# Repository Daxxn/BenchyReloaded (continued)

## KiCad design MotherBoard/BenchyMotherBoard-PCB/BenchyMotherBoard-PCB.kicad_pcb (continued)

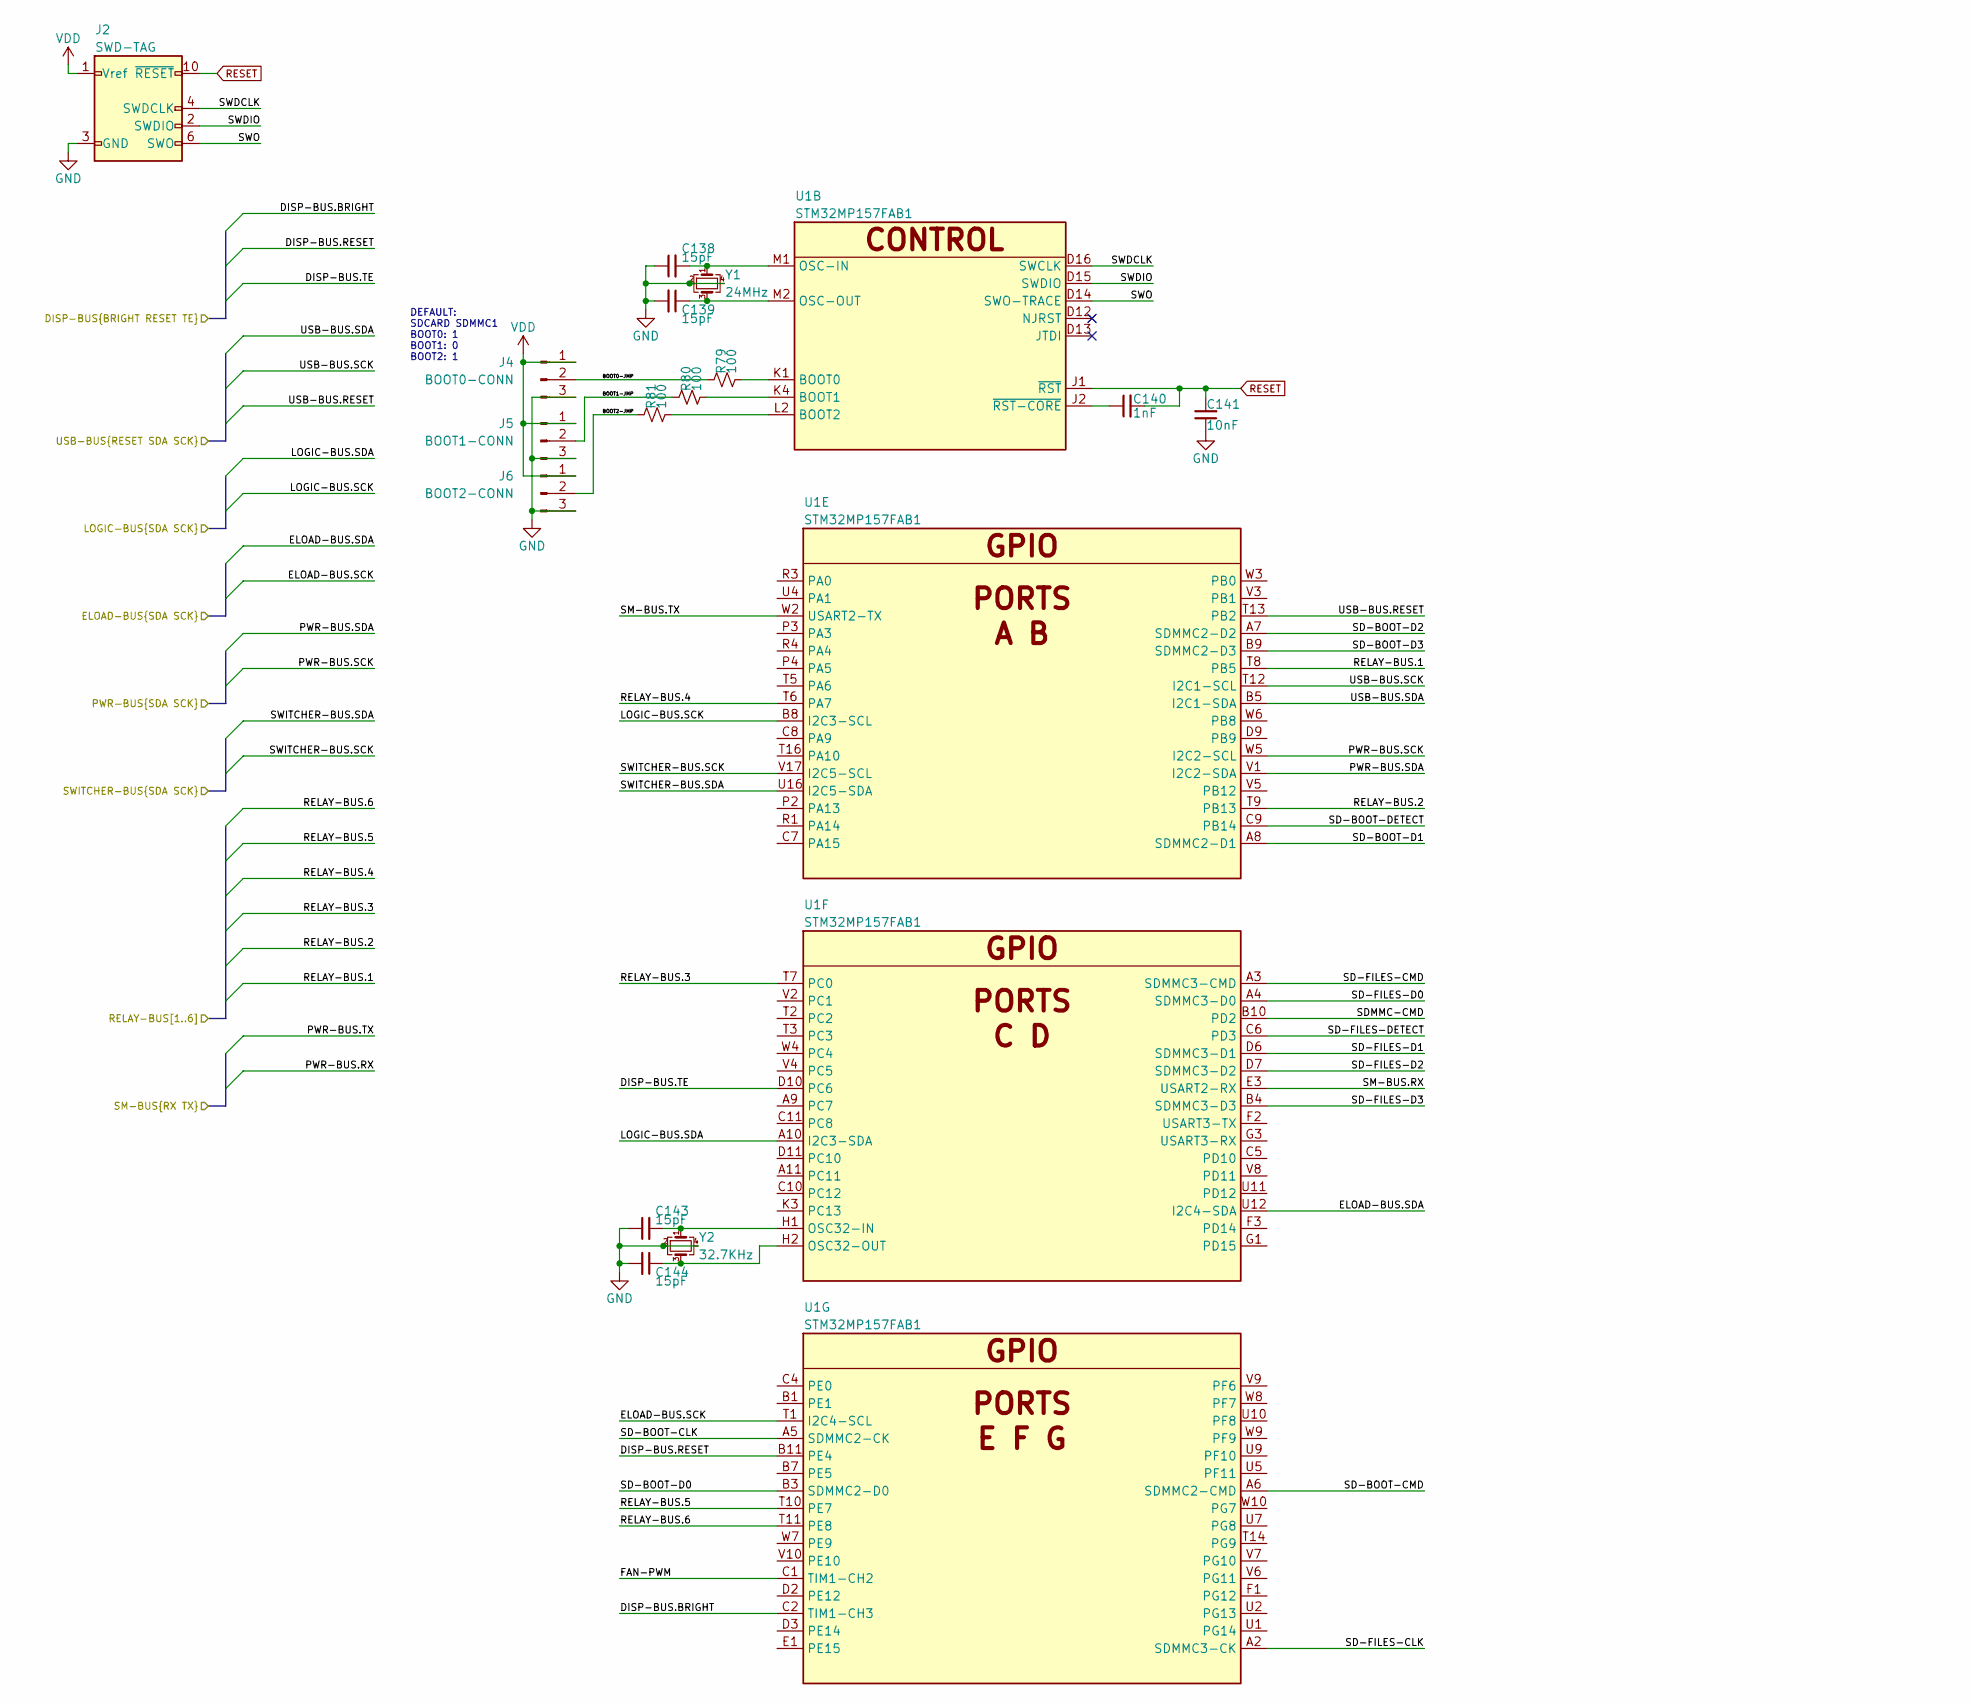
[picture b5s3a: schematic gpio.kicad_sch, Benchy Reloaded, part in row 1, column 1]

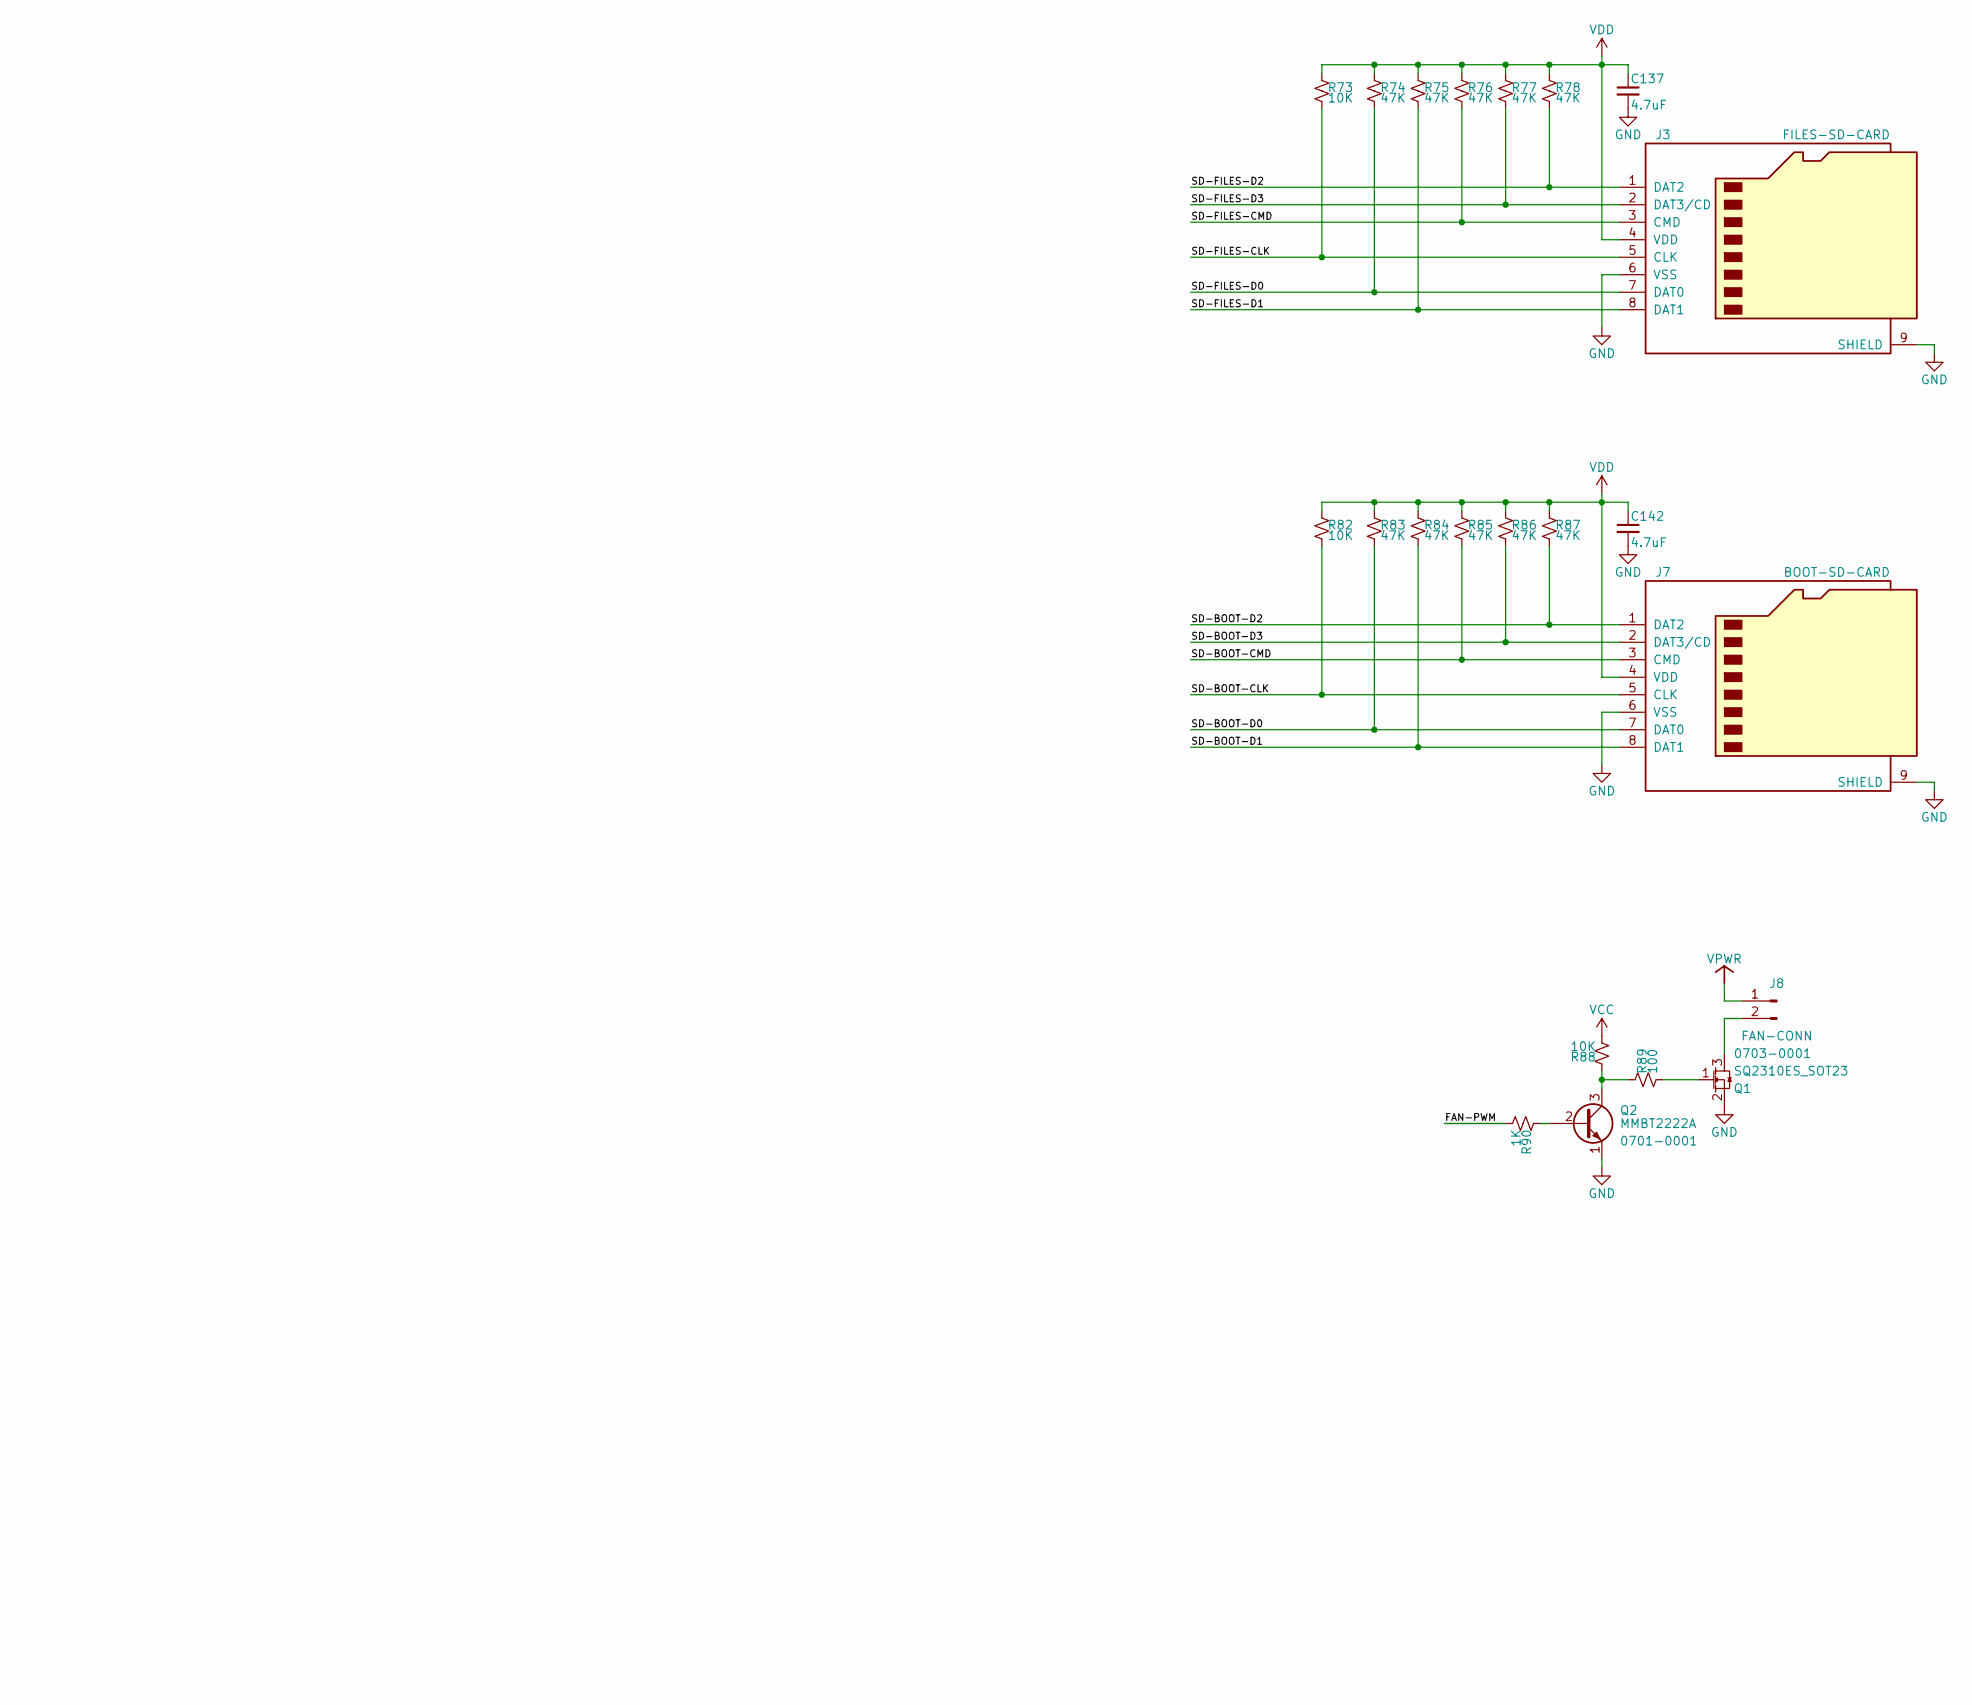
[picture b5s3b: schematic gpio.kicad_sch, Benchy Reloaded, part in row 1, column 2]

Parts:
C137, C142: 4.7uF; C_0805_2012Metric
C138, C139, C143, C144: 15pF; C_0402_1005Metric
C140: 1nF; C_0402_1005Metric
C141: 10nF; C_0402_1005Metric
J2: SWD-TAG; Tag-Connect_TC2050-IDC-FP_2x05_P1.27mm_Vertical
J3: FILES-SD-CARD; microSD_HC_Molex_47219-2001
J4: BOOT0-CONN; PinHeader_1x03_P2.54mm_Vertical
J5: BOOT1-CONN; PinHeader_1x03_P2.54mm_Vertical
J6: BOOT2-CONN; PinHeader_1x03_P2.54mm_Vertical
J7: BOOT-SD-CARD; microSD_HC_Molex_47219-2001
J8: FAN-CONN; PinHeader_1x02_P2.54mm_Vertical
Q1: SQ2310ES_SOT23; SOT-23; PartNumber 0703-0001
Q2: MMBT2222A; SOT-23; PartNumber 0701-0001
R73, R82, R88: 10K; R_0402_1005Metric
R74, R75, R76, R77, R78, R83, R84, R85, R86, R87: 47K; R_0402_1005Metric
R79, R80, R81, R89: 100; R_0402_1005Metric
R90: 1K; R_0402_1005Metric
U1: STM32MP157FAB1; LFBGA354-P0.8mm
Y1: 24MHz; Crystal_SMD_4Pin_3.2x2.5mm
Y2: 32.7KHz; Crystal_SMD_4Pin_3.2x2.5mm

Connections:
/COMMUNICATIONS/ELOAD-BUS.SCK: U1.T1 (I2C4-SCL); also elsewhere on the board
/COMMUNICATIONS/ELOAD-BUS.SDA: U1.U12 (I2C4-SDA); also elsewhere on the board
/COMMUNICATIONS/LOGIC-BUS.SCK: U1.B8 (I2C3-SCL); also elsewhere on the board
/COMMUNICATIONS/LOGIC-BUS.SDA: U1.A10 (I2C3-SDA); also elsewhere on the board
/COMMUNICATIONS/PWR-BUS.SCK: U1.W5 (I2C2-SCL); also elsewhere on the board
/COMMUNICATIONS/PWR-BUS.SDA: U1.V1 (I2C2-SDA); also elsewhere on the board
/COMMUNICATIONS/SWITCHER-BUS.SCK: U1.V17 (I2C5-SCL); also elsewhere on the board
/COMMUNICATIONS/SWITCHER-BUS.SDA: U1.U16 (I2C5-SDA); also elsewhere on the board
/INPUT | OUTPUT/BOOT0-JMP: J4.2, R79.1
/INPUT | OUTPUT/BOOT1-JMP: J5.2, R80.1
/INPUT | OUTPUT/BOOT2-JMP: J6.2, R81.1
/INPUT | OUTPUT/DISP-BUS.BRIGHT: U1.C2 (TIM1-CH3)
/INPUT | OUTPUT/DISP-BUS.RESET: U1.B11 (PE4); also elsewhere on the board
/INPUT | OUTPUT/DISP-BUS.TE: U1.D10 (PC6); also elsewhere on the board
/INPUT | OUTPUT/FAN-PWM: R90.2, U1.C1 (TIM1-CH2)
/INPUT | OUTPUT/RELAY-BUS.1: U1.T8 (PB5)
/INPUT | OUTPUT/RELAY-BUS.2: U1.T9 (PB13)
/INPUT | OUTPUT/RELAY-BUS.3: U1.T7 (PC0)
/INPUT | OUTPUT/RELAY-BUS.4: U1.T6 (PA7)
/INPUT | OUTPUT/RELAY-BUS.5: U1.T10 (PE7)
/INPUT | OUTPUT/RELAY-BUS.6: U1.T11 (PE8)
/INPUT | OUTPUT/SD-BOOT-CLK: J7.5 (CLK), R82.2, U1.A5 (SDMMC2-CK)
/INPUT | OUTPUT/SD-BOOT-CMD: J7.3 (CMD), R85.2, U1.A6 (SDMMC2-CMD)
/INPUT | OUTPUT/SD-BOOT-D0: J7.7 (DAT0), R83.2, U1.B3 (SDMMC2-D0)
/INPUT | OUTPUT/SD-BOOT-D1: J7.8 (DAT1), R84.2, U1.A8 (SDMMC2-D1)
/INPUT | OUTPUT/SD-BOOT-D2: J7.1 (DAT2), R87.2, U1.A7 (SDMMC2-D2)
/INPUT | OUTPUT/SD-BOOT-D3: J7.2 (DAT3/CD), R86.2, U1.B9 (SDMMC2-D3)
/INPUT | OUTPUT/SD-BOOT-DETECT: U1.C9 (PB14)
/INPUT | OUTPUT/SD-FILES-CLK: J3.5 (CLK), R73.2, U1.A2 (SDMMC3-CK)
/INPUT | OUTPUT/SD-FILES-CMD: J3.3 (CMD), R76.2, U1.A3 (SDMMC3-CMD)
/INPUT | OUTPUT/SD-FILES-D0: J3.7 (DAT0), R74.2, U1.A4 (SDMMC3-D0)
/INPUT | OUTPUT/SD-FILES-D1: J3.8 (DAT1), R75.2, U1.D6 (SDMMC3-D1)
/INPUT | OUTPUT/SD-FILES-D2: J3.1 (DAT2), R78.2, U1.D7 (SDMMC3-D2)
/INPUT | OUTPUT/SD-FILES-D3: J3.2 (DAT3/CD), R77.2, U1.B4 (SDMMC3-D3)
/INPUT | OUTPUT/SD-FILES-DETECT: U1.C6 (PD3)
/INPUT | OUTPUT/SDMMC-CMD: U1.B10 (PD2)
/INPUT | OUTPUT/SM-BUS.RX: U1.E3 (USART2-RX); also elsewhere on the board
/INPUT | OUTPUT/SM-BUS.TX: U1.W2 (USART2-TX); also elsewhere on the board
/INPUT | OUTPUT/SWDCLK: J2.4 (SWDCLK), U1.D16 (SWCLK)
/INPUT | OUTPUT/SWDIO: J2.2 (SWDIO), U1.D15 (SWDIO)
/INPUT | OUTPUT/SWO: J2.6 (SWO), U1.D14 (SWO-TRACE)
/INPUT | OUTPUT/USB-BUS.RESET: U1.T13 (PB2); also elsewhere on the board
/INPUT | OUTPUT/USB-BUS.SCK: U1.T12 (I2C1-SCL); also elsewhere on the board
/INPUT | OUTPUT/USB-BUS.SDA: U1.B5 (I2C1-SDA); also elsewhere on the board
GND: C137.2, C138.1, C139.2, C141.1, C142.2, C143.1, C144.2, J2.3 (GND), J2.5 (GND), J2.9 (GNDDetect), J3.6 (VSS), J3.9 (SHIELD), J4.3, J5.3, J6.3, J7.6 (VSS), J7.9 (SHIELD), Q1.2 (S), Q2.1 (E), Y1.2, Y1.4, Y2.2, Y2.4; also elsewhere on the board
unnamed: C138.2, U1.M1 (OSC-IN), Y1.1
unnamed: C139.1, U1.M2 (OSC-OUT), Y1.3
unnamed: C140.1, U1.J2 (~RST-CORE)
unnamed: C143.2, U1.H1 (OSC32-IN), Y2.1
unnamed: C144.1, U1.H2 (OSC32-OUT), Y2.3
unnamed: J8.2, Q1.3 (D)
unnamed: Q1.1 (G), R89.2
unnamed: Q2.2 (B), R90.1
unnamed: Q2.3 (C), R88.1, R89.1
unnamed: R79.2, U1.K1 (BOOT0)
unnamed: R80.2, U1.K4 (BOOT1)
unnamed: R81.2, U1.L2 (BOOT2)
RESET: C140.2, C141.2, J2.10 (~RESET), U1.J1 (~RST); also elsewhere on the board
VCC: R88.2; also elsewhere on the board
VDD: C137.1, C142.1, J2.1 (Vref), J3.4 (VDD), J4.1, J5.1, J6.1, J7.4 (VDD), R73.1, R74.1, R75.1, R76.1, R77.1, R78.1, R82.1, R83.1, R84.1, R85.1, R86.1, R87.1; also elsewhere on the board
VPWR: J8.1; also elsewhere on the board

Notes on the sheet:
DEFAULT: SDCARD SDMMC1 BOOT0: 1 BOOT1: 0 BOOT2: 1

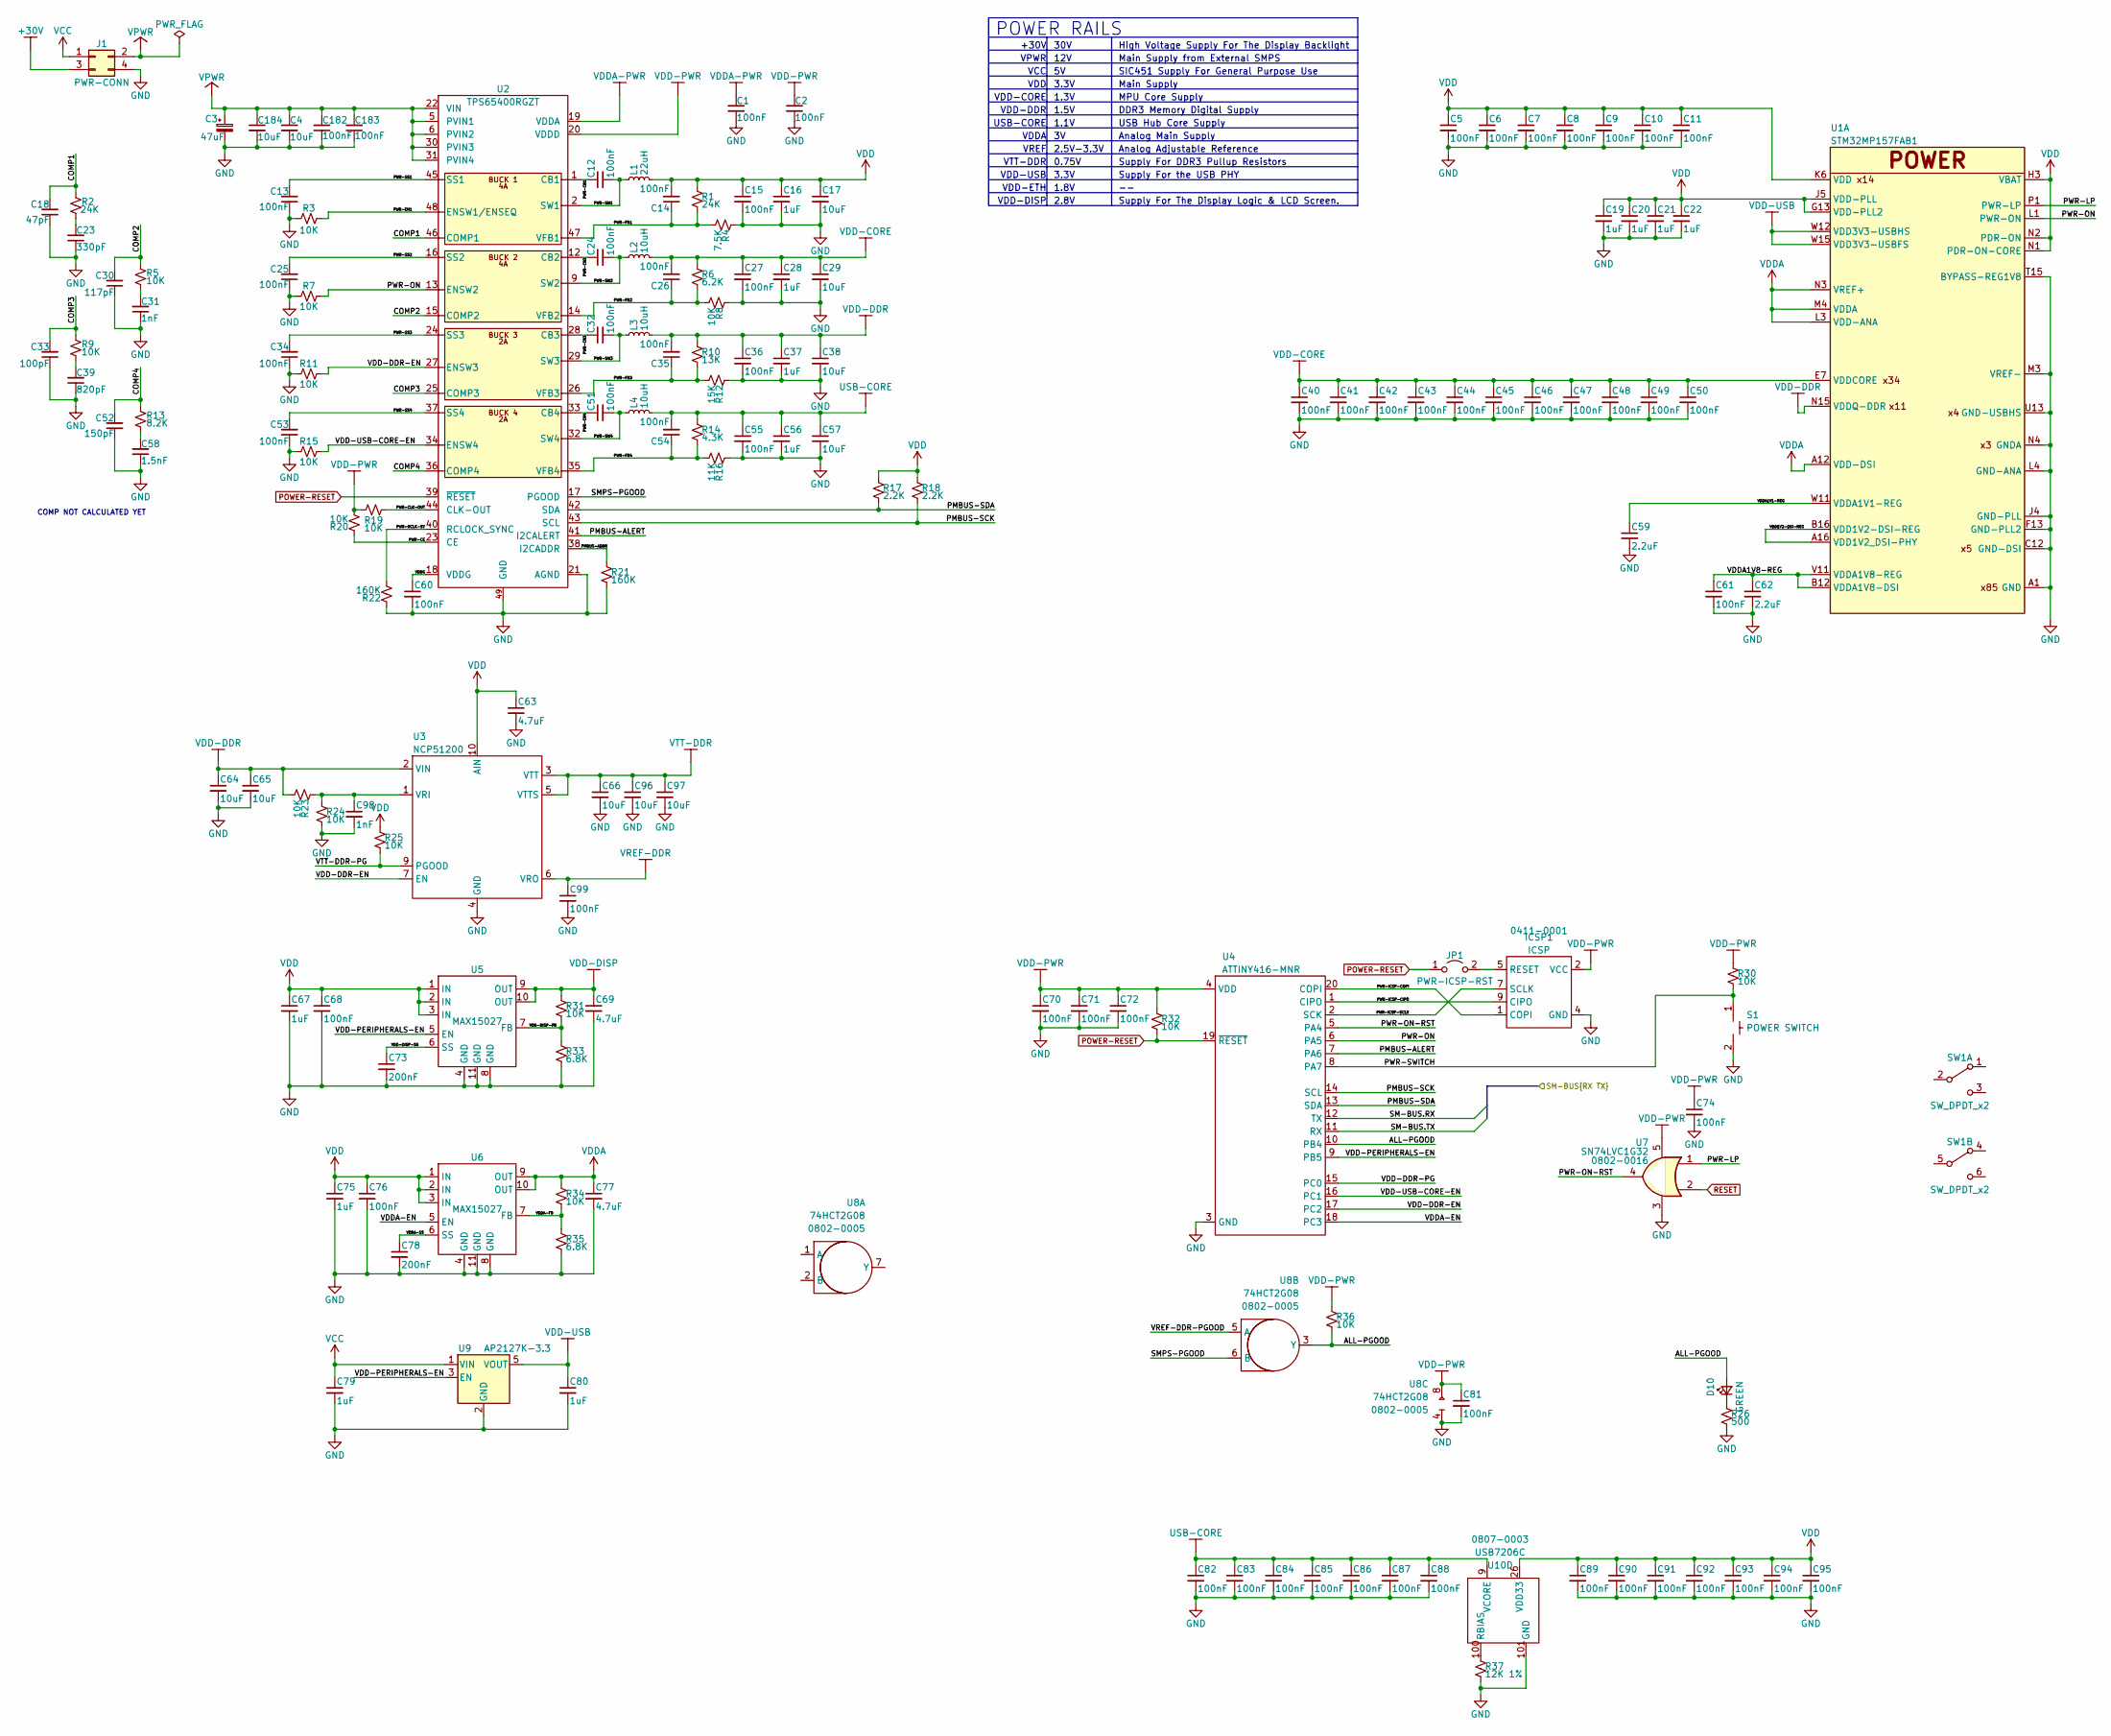
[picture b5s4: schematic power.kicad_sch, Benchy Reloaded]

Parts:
C1, C2: 100nF; C_0603_1608Metric
C3: 47uF; CP_Elec_6.3x7.7
C4, C17, C29, C38, C57, C184: 10uF; C_1210_3225Metric
C5, C6, C7, C8, C9, C10, C11, C12, C13, C14, C15, C24, C25, C26, C27, C32, C34, C35, C36, C40, C41, C42, C43, C44, C45, C46, C47, C48, C49, C50, C51, C53, C54, C55, C60, C61, C68, C70, C71, C72, C74, C76, C81, C82, C83, C84, C85, C86, C87, C88, C89, C90, C91, C92, C93, C94, C95, C99, C182, C183: 100nF; C_0402_1005Metric
C16, C19, C20, C21, C22, C28, C37, C56, C67, C75, C79, C80: 1uF; C_0603_1608Metric
C18: 47pF; C_0402_1005Metric
C23: 330pF; C_0402_1005Metric
C30: 117pF; C_0402_1005Metric
C31, C98: 1nF; C_0402_1005Metric
C33: 100pF; C_0402_1005Metric
C39: 820pF; C_0402_1005Metric
C52: 150pF; C_0402_1005Metric
C58: 1.5nF; C_0402_1005Metric
C59, C62: 2.2uF; C_0603_1608Metric
C63, C69, C77: 4.7uF; C_0603_1608Metric
C64, C65, C66, C96, C97: 10uF; C_0805_2012Metric
C73, C78: 200nF; C_0402_1005Metric
D10: GREEN; LED_0805_2012Metric
ICSP1: ICSP; Tag-Connect_TC2050-IDC-FP_2x05_P1.27mm_Vertical; PartNumber 0411-0001
J1: PWR-CONN; 4-Pin_Molex_Mini-Fit_Jr_Vertical_Mount
JP1: PWR-ICSP-RST; PinHeader_1x02_P2.54mm_Vertical
L1: 22uH; PA4341
L2, L3, L4: 10uH; PA4341
R1: 24K; C_0402_1005Metric
R2: 24K; R_0402_1005Metric
R3, R5, R7, R9, R11, R15, R19, R20, R23, R24, R25, R30, R31, R32, R34, R36: 10K; R_0402_1005Metric
R4: 7.5K; C_0402_1005Metric
R6: 6.2K; C_0402_1005Metric
R8: 10K; C_0402_1005Metric
R10: 13K; C_0402_1005Metric
R12: 15K; C_0402_1005Metric
R13: 8.2K; R_0402_1005Metric
R14: 4.3K; C_0402_1005Metric
R16: 11K; C_0402_1005Metric
R17, R18: 2.2K; R_0402_1005Metric
R21: 160K; C_0402_1005Metric
R22: 160K; R_0402_1005Metric
R26: 500; R_0603_1608Metric
R33, R35: 6.8K; R_0402_1005Metric
R37: 12K 1%; R_0402_1005Metric
S1: POWER SWITCH; TL3365AF180QG; PartNumber 1101-0000
SW1: SW_DPDT_x2; PHAP4383V
U1: STM32MP157FAB1; LFBGA354-P0.8mm
U2: TPS65400RGZT; QFN-48-1EP_7x7mm_P0.5mm_EP5.15x5.15mm_ThermalVias
U3: NCP51200; DFN-10-1EP_3x3mm_P0.5mm_EP1.7x2.5mm
U4: ATTINY416-MNR; VQFN-20-1EP_3x3mm_P0.4mm_EP1.7x1.7mm
U5, U6: MAX15027; DFN-10-1EP_3x3mm_P0.5mm_EP1.65x2.38mm
U7: SN74LVC1G32; SOT-23-5; PartNumber 0802-0016
U8: 74HCT2G08; TSSOP-8_3x3mm_P0.65mm; PartNumber 0802-0005
U9: AP2127K-3.3; SOT-23-5
U10: USB7206C; 100-VQFN-GND_12X12; PartNumber 0807-0003

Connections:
+30V: J1.3; also elsewhere on the board
/INPUT | OUTPUT/SM-BUS.RX: U4.12 (TX); also elsewhere on the board
/INPUT | OUTPUT/SM-BUS.TX: U4.11 (RX); also elsewhere on the board
/POWER/ALL-PGOOD: D10.2 (A), R36.2, U4.10 (PB4), U8.3 (Y)
/POWER/COMP1: C18.2, R2.1, U2.46 (COMP1)
/POWER/COMP2: C30.2, R5.1, U2.15 (COMP2)
/POWER/COMP3: C33.2, R9.1, U2.25 (COMP3)
/POWER/COMP4: C52.2, R13.1, U2.36 (COMP4)
/POWER/PMBUS-ADDR: R21.1, U2.38 (I2CADDR)
/POWER/PMBUS-ALERT: U2.41 (I2CALERT), U4.7 (PA6)
/POWER/PMBUS-SCK: R18.2, U2.43 (SCL), U4.14 (SCL)
/POWER/PMBUS-SDA: R17.2, U2.42 (SDA), U4.13 (SDA)
/POWER/PWR-CB1: C12.1, U2.1 (CB1)
/POWER/PWR-CB2: C24.1, U2.12 (CB2)
/POWER/PWR-CB3: C32.1, U2.28 (CB3)
/POWER/PWR-CB4: C51.1, U2.33 (CB4)
/POWER/PWR-CE: R20.1, U2.23 (CE)
/POWER/PWR-CLK-OUT: R19.2, U2.44 (CLK-OUT)
/POWER/PWR-EN1: R3.1, U2.48 (ENSW1/ENSEQ)
/POWER/PWR-FB1: C14.1, R1.2, R4.2, U2.47 (VFB1)
/POWER/PWR-FB2: C26.1, R6.2, R8.2, U2.14 (VFB2)
/POWER/PWR-FB3: C35.1, R10.2, R12.2, U2.26 (VFB3)
/POWER/PWR-FB4: C54.1, R14.2, R16.2, U2.35 (VFB4)
/POWER/PWR-ICSP-CIPO: ICSP1.9 (CIPO), U4.1 (CIPO)
/POWER/PWR-ICSP-COPI: ICSP1.1 (COPI), U4.20 (COPI)
/POWER/PWR-ICSP-SCLK: ICSP1.7 (SCLK), U4.2 (SCK)
/POWER/PWR-LP: U1.P1 (PWR-LP), U7.1
/POWER/PWR-ON: R7.1, U1.L1 (PWR-ON), U2.13 (ENSW2), U4.6 (PA5)
/POWER/PWR-ON-RST: U4.5 (PA4), U7.4
/POWER/PWR-RCLK-SY: R22.2, U2.40 (RCLOCK_SYNC)
/POWER/PWR-SS1: C13.2, U2.45 (SS1)
/POWER/PWR-SS2: C25.2, U2.16 (SS2)
/POWER/PWR-SS3: C34.2, U2.24 (SS3)
/POWER/PWR-SS4: C53.2, U2.37 (SS4)
/POWER/PWR-SW1: C12.2, L1.1, U2.2 (SW1), U2.3 (SW1), U2.4 (SW1)
/POWER/PWR-SW2: C24.2, L2.1, U2.9 (SW2), U2.10 (SW2), U2.11 (SW2)
/POWER/PWR-SW3: C32.2, L3.1, U2.29 (SW3)
/POWER/PWR-SW4: C51.2, L4.1, U2.32 (SW4)
/POWER/PWR-SWITCH: R30.2, S1.1, U4.8 (PA7)
/POWER/SMPS-PGOOD: U2.17 (PGOOD), U8.6 (B)
/POWER/VDD1V2-DSI-REG: U1.A16 (VDD1V2_DSI-PHY), U1.B16 (VDD1V2-DSI-REG)
/POWER/VDD-DDR-EN: R11.1, U2.27 (ENSW3), U3.7 (EN), U4.17 (PC2)
/POWER/VDD-DDR-PG: U4.15 (PC0)
/POWER/VDD-DISP-FB: R31.2, R33.1, U5.7 (FB)
/POWER/VDD-DISP-SS: C73.1, U5.6 (SS)
/POWER/VDD-PERIPHERALS-EN: U4.9 (PB5), U5.5 (EN), U9.3 (EN)
/POWER/VDD-USB-CORE-EN: R15.1, U2.34 (ENSW4), U4.16 (PC1)
/POWER/VDDA1V1-REG: C59.1, U1.W11 (VDDA1V1-REG)
/POWER/VDDA1V8-REG: C61.1, C62.1, U1.B12 (VDDA1V8-DSI), U1.V11 (VDDA1V8-REG)
/POWER/VDDA-EN: U4.18 (PC3), U6.5 (EN)
/POWER/VDDA-FB: R34.2, R35.1, U6.7 (FB)
/POWER/VDDA-SS: C78.1, U6.6 (SS)
/POWER/VDDG: C60.1, U2.18 (VDDG)
/POWER/VREF-DDR-PGOOD: U8.5 (A)
/POWER/VTT-DDR-PG: R25.2, U3.9 (PGOOD)
GND: C1.2, C2.2, C3.2, C4.2, C5.2, C6.2, C7.2, C8.2, C9.2, C10.2, C11.2, C13.1, C15.2, C16.2, C17.2, C18.1, C19.2, C20.2, C21.2, C22.2, C23.1, C25.1, C27.2, C28.2, C29.2, C30.1, C31.1, C33.1, C34.1, C36.2, C37.2, C38.2, C39.1, C40.2, C41.2, C42.2, C43.2, C44.2, C45.2, C46.2, C47.2, C48.2, C49.2, C50.2, C52.1, C53.1, C55.2, C56.2, C57.2, C58.1, C59.2, C60.2, C61.2, C62.2, C63.2, C64.2, C65.2, C66.2, C67.2, C68.2, C69.2, C70.2, C71.2, C72.2, C73.2, C74.2, C75.2, C76.2, C77.2, C78.2, C79.2, C80.2, C81.2, C82.2, C83.2, C84.2, C85.2, C86.2, C87.2, C88.2, C89.2, C90.2, C91.2, C92.2, C93.2, C94.2, C95.2, C96.2, C97.2, C98.2, C99.2, C182.1, C183.1, C184.2, ICSP1.4 (GND), ICSP1.6 (GND), ICSP1.8 (GND), ICSP1.10 (GND), J1.4, R3.2, R4.1, R7.2, R8.1, R11.2, R12.1, R15.2, R16.1, R21.2, R22.1, R24.2, R26.2, R33.2, R35.2, R37.2, S1.2, U1.A1 (GND), U1.A19 (GND), U1.B2 (GND), U1.B6 (GND), U1.C3 (GND), U1.C12 (GND-DSI), U1.C13 (GND-DSI), U1.C14 (GND-DSI), U1.C15 (GND-DSI), U1.C16 (GND-DSI), U1.C17 (GND), U1.D1 (GND), U1.D4 (GND), U1.D5 (GND), U1.D8 (GND), U1.E2 (GND), U1.E4 (GND), U1.E5 (GND), U1.E6 (GND), U1.E8 (GND), U1.E10 (GND), U1.E12 (GND), U1.E14 (GND), U1.E16 (GND), U1.F5 (GND), U1.F7 (GND), U1.F9 (GND), U1.F11 (GND), U1.F13 (GND-PLL2), U1.F15 (GND), U1.G2 (GND), U1.G4 (GND), U1.G6 (GND), U1.G8 (GND), U1.G10 (GND), U1.G12 (GND), U1.G14 (GND), U1.H5 (GND), U1.H7 (GND), U1.H9 (GND), U1.H11 (GND), U1.H13 (GND), U1.H15 (GND), U1.J3 (GND), U1.J4 (GND-PLL), U1.J6 (GND), U1.J8 (GND), U1.J10 (GND), U1.J12 (GND), U1.J14 (GND), U1.K2 (GND), U1.K5 (GND), U1.K7 (GND), U1.K9 (GND), U1.K11 (GND), U1.K13 (GND), U1.K15 (GND), U1.L4 (GND-ANA), U1.L6 (GND), U1.L8 (GND), U1.L10 (GND), U1.L12 (GND), U1.L14 (GND), U1.M3 (VREF-), U1.M5 (GND), U1.M7 (GND), U1.M9 (GND), U1.M11 (GND), U1.M13 (GND), U1.M15 (GND), U1.N4 (GNDA), U1.N6 (GND), U1.N8 (GND), U1.N10 (GND), U1.N12 (GND), U1.N14 (GND), U1.P5 (GNDA), U1.P7 (GND), U1.P9 (GND), U1.P11 (GND), U1.P13 (GND), U1.P15 (GND), U1.R2 (GND), U1.R5 (GNDA), U1.R6 (GND), U1.R8 (GND), U1.R10 (GND), U1.R12 (GND), U1.R14 (GND), U1.R16 (GND), U1.T4 (GND), U1.T15 (BYPASS-REG1V8), U1.U3 (GND), U1.U6 (GND), U1.U8 (GND), U1.U13 (GND-USBHS), U1.U14 (GND-USBHS), U1.U17 (GND), U1.V12 (GND-USBHS), U1.V15 (GND-USBHS), U1.W1 (GND), U1.W19 (GND), U2.7 (PGND), U2.8 (PGND), U2.21 (AGND), U2.49 (GND), U3.4 (GND), U3.8 (GND), U3.11 (GND), U4.3 (GND), U4.21 (GND), U5.4 (GND), U5.8 (GND), U5.11 (GND), U6.4 (GND), U6.8 (GND), U6.11 (GND), U7.3, U8.4, U9.2 (GND), U10.101 (GND); also elsewhere on the board
unnamed: C23.2, R2.2
unnamed: C31.2, R5.2
unnamed: C39.2, R9.2
unnamed: C58.2, R13.2
unnamed: C98.1, R23.1, R24.1, U3.1 (VRI)
unnamed: D10.1 (K), R26.1
unnamed: ICSP1.5 (RESET), JP1.2 (B)
unnamed: R37.1, U10.100 (RBIAS)
POWER-RESET: JP1.1 (A), R32.2, U2.39 (~RESET), U4.19 (~RESET)
RESET: U7.2; also elsewhere on the board
USB-CORE: C54.2, C55.1, C56.1, C57.1, C82.1, C83.1, C84.1, C85.1, C86.1, C87.1, C88.1, L4.2, R14.1, U10.9 (VCORE), U10.18 (VCORE), U10.25 (VCORE), U10.31 (VCORE), U10.38 (VCORE), U10.55 (VCORE), U10.78 (VCORE), U10.85 (VCORE), U10.93 (VCORE)
VCC: C79.1, J1.1, U9.1 (VIN); also elsewhere on the board
VDD: C5.1, C6.1, C7.1, C8.1, C9.1, C10.1, C11.1, C14.2, C15.1, C16.1, C17.1, C19.1, C20.1, C21.1, C22.1, C63.1, C67.1, C68.1, C75.1, C76.1, C89.1, C90.1, C91.1, C92.1, C93.1, C94.1, C95.1, L1.2, R1.1, R17.1, R18.1, R25.1, U1.G13 (VDD-PLL2), U1.H3 (VBAT), U1.J5 (VDD-PLL), U1.K6 (VDD), U1.L5 (VDD), U1.L7 (VDD), U1.M6 (VDD), U1.M8 (VDD), U1.N1 (PDR-ON-CORE), U1.N2 (PDR-ON), U1.N5 (VDD), U1.N7 (VDD), U1.N9 (VDD), U1.P6 (VDD), U1.P8 (VDD), U1.P10 (VDD), U1.R7 (VDD), U1.R9 (VDD), U1.R11 (VDD), U3.10 (AIN), U5.1 (IN), U5.2 (IN), U5.3 (IN), U6.1 (IN), U6.2 (IN), U6.3 (IN), U10.26 (VDD33), U10.43 (VDD33), U10.53 (VDD33), U10.62 (VDD33), U10.67 (VDD33), U10.79 (VDD33), U10.88 (VDD33), U10.99 (VDD33); also elsewhere on the board
VDD-CORE: C26.2, C27.1, C28.1, C29.1, C40.1, C41.1, C42.1, C43.1, C44.1, C45.1, C46.1, C47.1, C48.1, C49.1, C50.1, L2.2, R6.1, U1.E7 (VDDCORE), U1.E9 (VDDCORE), U1.E11 (VDDCORE), U1.E13 (VDDCORE), U1.F4 (VDDCORE), U1.F6 (VDDCORE), U1.F8 (VDDCORE), U1.F10 (VDDCORE), U1.F12 (VDDCORE), U1.G5 (VDDCORE), U1.G7 (VDDCORE), U1.G9 (VDDCORE), U1.G11 (VDDCORE), U1.H4 (VDDCORE), U1.H6 (VDDCORE), U1.H8 (VDDCORE), U1.H10 (VDDCORE), U1.H12 (VDDCORE), U1.J7 (VDDCORE), U1.J9 (VDDCORE), U1.J11 (VDDCORE), U1.J13 (VDDCORE), U1.K8 (VDDCORE), U1.K10 (VDDCORE), U1.K12 (VDDCORE), U1.L9 (VDDCORE), U1.L11 (VDDCORE), U1.L13 (VDDCORE), U1.M10 (VDDCORE), U1.M12 (VDDCORE), U1.N11 (VDDCORE), U1.N13 (VDDCORE), U1.P12 (VDDCORE), U1.R13 (VDDCORE)
VDD-DDR: C35.2, C36.1, C37.1, C38.1, C64.1, C65.1, L3.2, R10.1, R23.2, U1.E15 (VDDQ-DDR), U1.F14 (VDDQ-DDR), U1.G15 (VDDQ-DDR), U1.H14 (VDDQ-DDR), U1.J15 (VDDQ-DDR), U1.K14 (VDDQ-DDR), U1.L15 (VDDQ-DDR), U1.M14 (VDDQ-DDR), U1.N15 (VDDQ-DDR), U1.P14 (VDDQ-DDR), U1.R15 (VDDQ-DDR), U3.2 (VIN); also elsewhere on the board
VDD-DISP: C69.1, R31.1, U5.9 (OUT), U5.10 (OUT)
VDD-PWR: C2.1, C70.1, C71.1, C72.1, C74.1, C81.1, ICSP1.2 (VCC), R19.1, R20.2, R30.1, R32.1, R36.1, U2.20 (VDDD), U4.4 (VDD), U7.5, U8.8
VDD-USB: C80.1, U1.W12 (VDD3V3-USBHS), U1.W15 (VDD3V3-USBFS), U9.5 (VOUT)
VDDA: C77.1, R34.1, U1.A12 (VDD-DSI), U1.L3 (VDD-ANA), U1.M4 (VDDA), U1.N3 (VREF+), U6.9 (OUT), U6.10 (OUT)
VDDA-PWR: C1.1, U2.19 (VDDA)
VPWR: C3.1, C4.1, C182.2, C183.2, C184.1, J1.2, U2.5 (PVIN1), U2.6 (PVIN2), U2.22 (VIN), U2.30 (PVIN3), U2.31 (PVIN4); also elsewhere on the board
VREF-DDR: C99.1, U3.6 (VRO); also elsewhere on the board
VTT-DDR: C66.1, C96.1, C97.1, U3.3 (VTT), U3.5 (VTTS); also elsewhere on the board

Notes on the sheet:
Supply For the USB PHY
2.5V-3.3V
VREF
VDD-DDR
1.1V
3.3V
VDD-ETH
2.8V
VDD-USB
VDDA
1.5V
VDD-DISP
Main Supply from External SMPS
COMP NOT CALCULATED YET
1.8V
POWER RAILS
VDD-CORE
MPU Core Supply
Analog Main Supply
12V
VCC
DDR3 Memory Digital Supply
High Voltage Supply For The Display Backlight
Supply For The Display Logic & LCD Screen.
30V
VDD
VTT-DDR
1.3V
VPWR
Main Supply
Supply For DDR3 Pullup Resistors
USB Hub Core Supply
Analog Adjustable Reference
0.75V
SIC451 Supply For General Purpose Use
+30V
USB-CORE

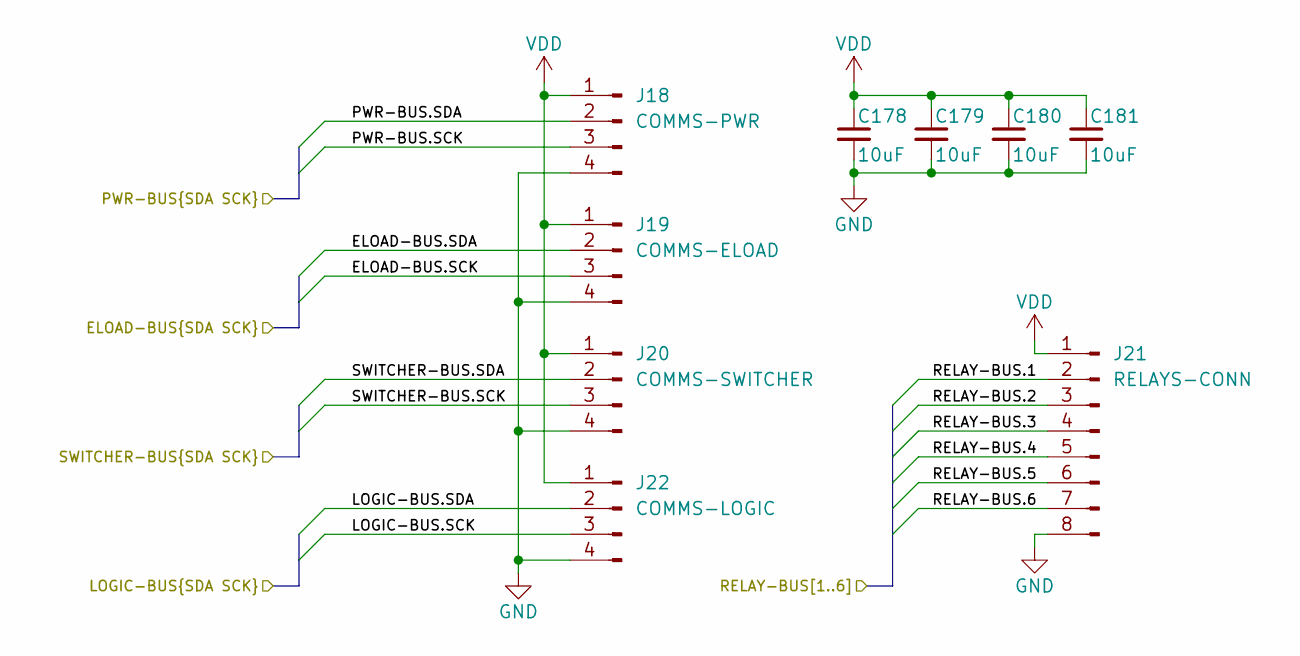
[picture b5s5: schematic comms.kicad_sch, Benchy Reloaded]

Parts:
C178, C179, C180, C181: 10uF; C_1210_3225Metric
J18: COMMS-PWR; JST_XH_B4B-XH-A_Vertical
J19: COMMS-ELOAD; JST_XH_B4B-XH-A_Vertical
J20: COMMS-SWITCHER; JST_XH_B4B-XH-A_Vertical
J21: RELAYS-CONN; JST_XH_B8B-XH-A_1x08_P2.50mm_Vertical
J22: COMMS-LOGIC; JST_XH_B4B-XH-A_Vertical

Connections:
/COMMUNICATIONS/ELOAD-BUS.SCK: J19.3; also elsewhere on the board
/COMMUNICATIONS/ELOAD-BUS.SDA: J19.2; also elsewhere on the board
/COMMUNICATIONS/LOGIC-BUS.SCK: J22.3; also elsewhere on the board
/COMMUNICATIONS/LOGIC-BUS.SDA: J22.2; also elsewhere on the board
/COMMUNICATIONS/PWR-BUS.SCK: J18.3; also elsewhere on the board
/COMMUNICATIONS/PWR-BUS.SDA: J18.2; also elsewhere on the board
/COMMUNICATIONS/RELAY-BUS.1: J21.2
/COMMUNICATIONS/RELAY-BUS.2: J21.3
/COMMUNICATIONS/RELAY-BUS.3: J21.4
/COMMUNICATIONS/RELAY-BUS.4: J21.5
/COMMUNICATIONS/RELAY-BUS.5: J21.6
/COMMUNICATIONS/RELAY-BUS.6: J21.7
/COMMUNICATIONS/SWITCHER-BUS.SCK: J20.3; also elsewhere on the board
/COMMUNICATIONS/SWITCHER-BUS.SDA: J20.2; also elsewhere on the board
GND: C178.2, C179.2, C180.2, C181.2, J18.4, J19.4, J20.4, J21.8, J22.4; also elsewhere on the board
VDD: C178.1, C179.1, C180.1, C181.1, J18.1, J19.1, J20.1, J21.1, J22.1; also elsewhere on the board
